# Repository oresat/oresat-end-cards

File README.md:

# "End Card" PCBs for OreSat

OreSat cards in the top position (#1) and bottom position (#20) are special because they interface with
both the solar arrays and with the end caps. They also tend to hold deployable antennas.

## Features

- 4 solar panel connectors
- 3 available RF connectors
- Alternative backplane connectors only (since the solar panel connectors take up the main connector spot)

## Connector information

- TBD.

## LICENSE

Copyright Portland State Aerospace Society 2022.

This documentation describes Open Hardware and is licensed under the CERN OHL v2

You may redistribute and modify this documentation under the terms of the CERN OHL v.1.2. [https://ohwr.org/cernohl](https://ohwr.org/cernohl). This documentation is distributed WITHOUT ANY EXPRESS OR IMPLIED WARRANTY, INCLUDING OF MERCHANTABILITY, SATISFACTORY QUALITY AND FITNESS FOR A PARTICULAR PURPOSE. Please see the CERN OHL v2 for applicable conditions.

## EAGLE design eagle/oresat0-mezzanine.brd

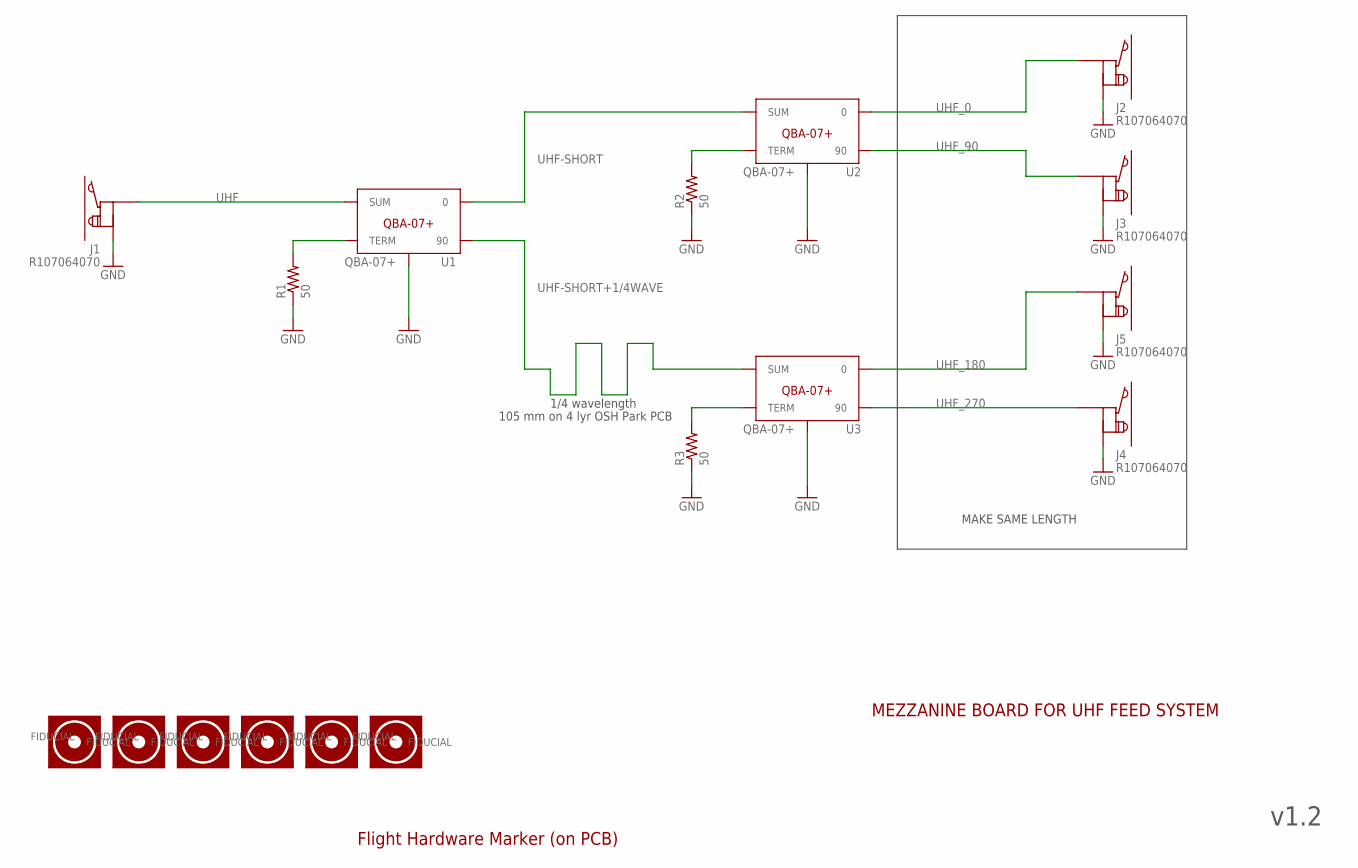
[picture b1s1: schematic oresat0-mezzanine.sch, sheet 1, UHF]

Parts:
FIDUCIAL1, FIDUCIAL2, FIDUCIAL3, FIDUCIAL4, FIDUCIAL6, FIDUCIAL7: FIDUCIAL-1.0X2.0
J1, J2, J3, J4, J5: R107064070; R107064070_SOLDER
R1, R2, R3: 50; .0603-C-NOSILK
U1, U2, U3: QBA-07+
U$1: FLIGHMARKERNEW; FLIGHTMARKER_NEW_BOARDS

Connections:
GND: J1.P$2, J1.P$3, J2.P$2, J2.P$3, J3.P$2, J3.P$3, J4.P$2, J4.P$3, J5.P$2, J5.P$3, R1.1, R2.1, R3.1, U1.2 (GND), U1.3 (GND), U1.4 (GND), U1.7 (GND), U1.8 (GND), U1.9 (GND), U1.GND-NO-PAD (GND), U2.2 (GND), U2.3 (GND), U2.4 (GND), U2.7 (GND), U2.8 (GND), U2.9 (GND), U2.GND-NO-PAD (GND), U3.2 (GND), U3.3 (GND), U3.4 (GND), U3.7 (GND), U3.8 (GND), U3.9 (GND), U3.GND-NO-PAD (GND); also elsewhere on the board
unnamed: R1.2, U1.5 (TERM)
unnamed: R2.2, U2.5 (TERM)
unnamed: R3.2, U3.5 (TERM)
UHF: J1.P$1, U1.1 (SUM)
UHF-SHORT: U1.6 (0), U2.1 (SUM)
UHF-SHORT+1/4WAVE: U1.10 (90), U3.1 (SUM)
UHF_0: J2.P$1, U2.6 (0)
UHF_90: J3.P$1, U2.10 (90)
UHF_180: J5.P$1, U3.6 (0)
UHF_270: J4.P$1, U3.10 (90)

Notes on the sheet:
1/4 wavelength
v1.2
MEZZANINE BOARD FOR UHF FEED SYSTEM
MAKE SAME LENGTH
105 mm on 4 lyr OSH Park PCB

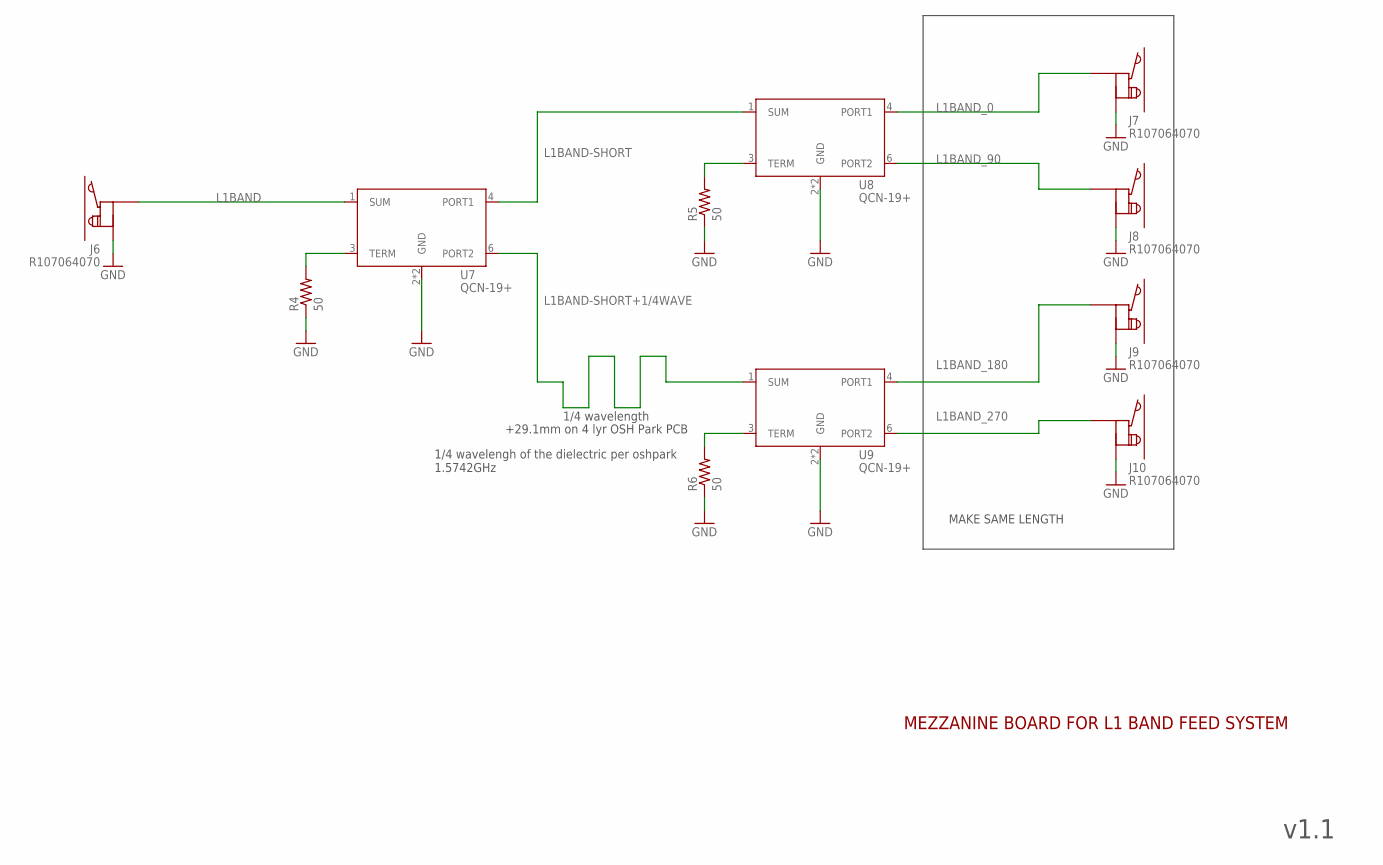
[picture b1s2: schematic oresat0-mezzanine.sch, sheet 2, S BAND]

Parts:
J6, J7, J8, J9, J10: R107064070; R107064070_SOLDER
R4, R5, R6: 50; .0603-C-NOSILK
U7, U8, U9: QCN-19+; QCN-XXX+

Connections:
GND: J6.P$2, J6.P$3, J7.P$2, J7.P$3, J8.P$2, J8.P$3, J9.P$2, J9.P$3, J10.P$2, J10.P$3, R4.1, R5.1, R6.1, U7.2 (GND), U7.5 (GND), U8.2 (GND), U8.5 (GND), U9.2 (GND), U9.5 (GND); also elsewhere on the board
L1BAND: J6.P$1, U7.1 (SUM)
L1BAND-SHORT: U7.4 (PORT1), U8.1 (SUM)
L1BAND-SHORT+1/4WAVE: U7.6 (PORT2), U9.1 (SUM)
L1BAND_0: J7.P$1, U8.4 (PORT1)
L1BAND_90: J8.P$1, U8.6 (PORT2)
L1BAND_180: J9.P$1, U9.4 (PORT1)
L1BAND_270: J10.P$1, U9.6 (PORT2)
unnamed: R4.2, U7.3 (TERM)
unnamed: R5.2, U8.3 (TERM)
unnamed: R6.2, U9.3 (TERM)

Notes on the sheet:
1/4 wavelength
v1.1
MEZZANINE BOARD FOR L1 BAND FEED SYSTEM
+29.1mm on 4 lyr OSH Park PCB
MAKE SAME LENGTH
1/4 wavelengh of the dielectric per oshpark 1.5742GHz

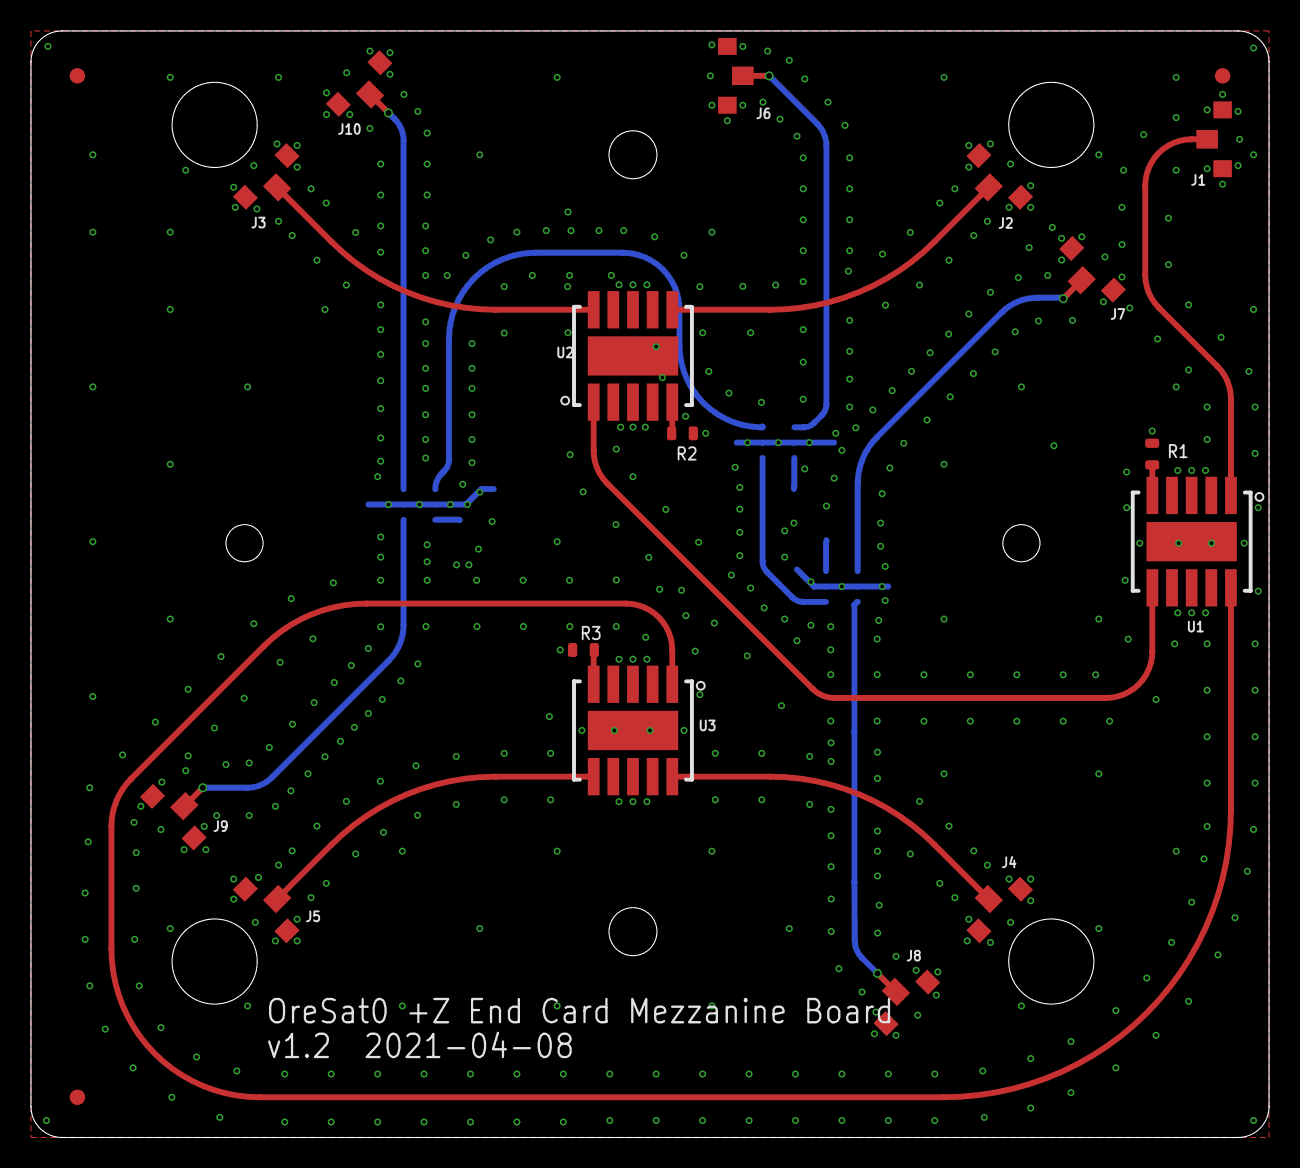
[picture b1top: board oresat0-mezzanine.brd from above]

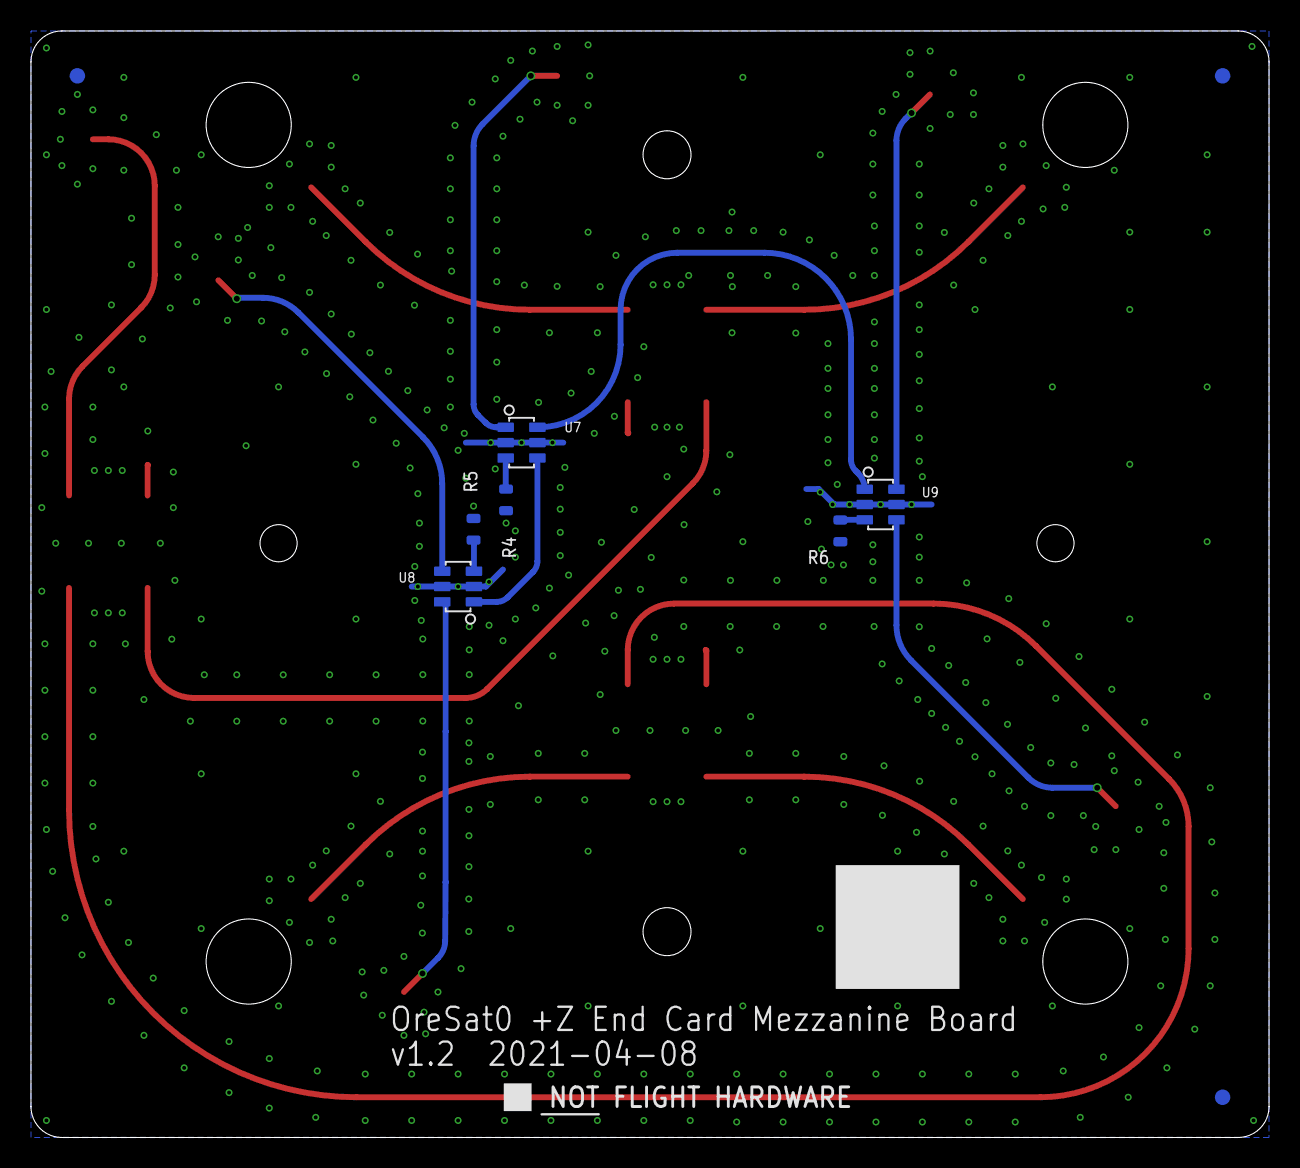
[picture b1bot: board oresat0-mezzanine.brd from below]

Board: 4 copper layers, 80.0 x 71.5 mm, 29 parts (10 on the bottom side), 21 nets.

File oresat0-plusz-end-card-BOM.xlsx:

Bill Of Materials for OreSat0 +Z End Card and Mezzanine
Last modified: 2021/11/01
PCB version: 2.0 |  |  | P/DNP = | Place/Do Not Place (DNP is for final production boards)
BOM revision: 0 |  |  | Generic = | Any generic part with the same characteristics are OK (e.g., bypass cap)
 | +Z END CARD
Cnt | Part References | P/DNP | Mfg | Mfg PN | Description | Generic | Dist | Dist Part Number | Cost | Cost Ext.
1 | CF1 | P | Harwin Inc. | M55-6001242R | 12 Position Receptacle Connector 0.050" (1.27mm) Surface Mount Gold | N | Digi-Key | 952-3835-1-ND | 1.74 | 1.74
3 | CM1, CM2, CM3 | P | Molex | 73300-0020 | SMPM Connector Plug, Male Pin 50Ohm Board Edge | N | Digi-Key | WM10772-ND | 16.41 | 49.230000000000004
4 | HW1, HW2, HW3, HW4 | P | McMaster Carr | 94100A150 | M2 x 0.4 mm 18-8 Stainless Steel Press-Fit Nut | N | McMaster Carr | 94100A150 | 0.56200000000000006 | 2.2480000000000002
4 | J1, J2, J3, J4 | P | Harwin Inc. | M55-7101242R | CONN HEADER SMD R/A 12POS 1.27MM -- Solar connectors | N | Digi-Key | 952-3891-1-ND | 1.46 | 5.8399999999999999
1 | J6 | P | Samtec Inc. | TFM-120-01-L-D-RA | CONN HEADER R/A 40POS 1.27MM - Main OreSat connector | N | Digi-Key | SAM10145-ND | 10.119999999999999 | 10.119999999999999
3 | R1, R2, R3 | P | Vishay Dale | RCP0603W50R0GEB | RES SMD 50 OHM 2% 1.5W 0603 | N | Digi-Key | 541-2655-1-ND | 1.8400000000000001 | 5.5200000000000005
1 | R4 | P | Vishay | PAC100007508FA1000 | Res 7.5 ohm 1W 1% Axial high temperature | N | Digi-Key | PPC1D1.0CT-ND | 0.77000000000000002 | 0.77000000000000002
3 | U1, U2, U3 | P | Mini-Circuits | QCN-19+ | Power Splitter/Combiner, 2 Way-90°, 50Ω, 1100-1925 Mhz, LTCC | N | Mouser | 139-QCN-19 | 13.949999999999999 | 41.849999999999994
 | MEZZANINE
Cnt | Part References | P/DNP | Mfg | Mfg PN | Description | Generic | Dist | Dist Part Number | Cost | Cost Ext.
10 | J1, J2, J3, J4, J5, J6, J7, J8, J9, J10 | P | Radiall | R107064070 | Spring RF connectors | N | Mouser | 501-R107064070 | 5.1500000000000004 | 51.5
6 | R1, R2, R3, R4, R5, R6 | P | Vishay Dale | RCP0603W50R0GEB | RES SMD 50 OHM 2% 1.5W 0603 | N | Digi-Key | 541-2655-1-ND | 1.8400000000000001 | 11.040000000000001
3 | U1, U2, U3 | P | Mini-Circuits | QBA-07+ | Power Splitter/Combiner, 2 Way-90°, 50Ω, 340-680 Mhz, LTCC | N | Mini-Circuits | QBA-07+ | 6.9500000000000002 | 20.850000000000001
3 | U7, U8, U9 | P | Mini-Circuits | QCN-19+ | Power Splitter/Combiner, 2 Way-90°, 50Ω, 1100-1925 Mhz, LTCC | N | Mouser | 139-QCN-19 | 13.949999999999999 | 41.849999999999994
 |  |  |  |  |  |  |  | Total |  | 242.55799999999999

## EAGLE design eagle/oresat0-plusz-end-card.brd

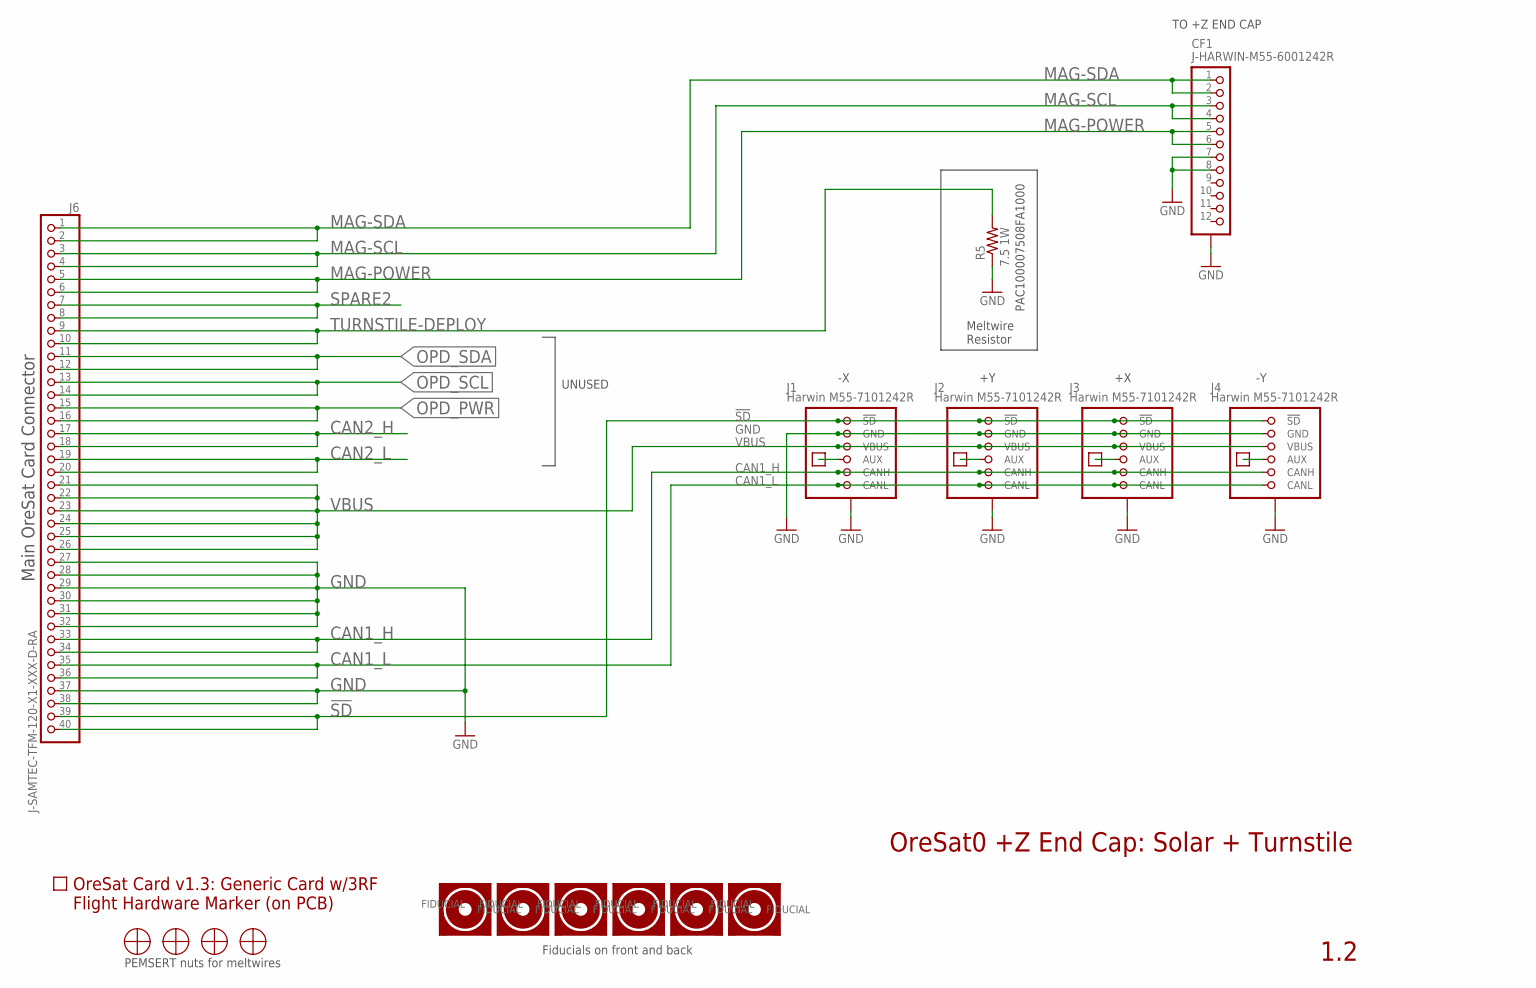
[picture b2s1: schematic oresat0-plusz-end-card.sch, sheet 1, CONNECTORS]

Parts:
CF1: J-HARWIN-M55-6001242R; HARWIN-M55-60X1242R
FIDUCIAL1, FIDUCIAL2, FIDUCIAL3, FIDUCIAL4, FIDUCIAL5, FIDUCIAL6: FIDUCIAL-1.0X2.0
HW1, HW2, HW3, HW4: MCMASTER-94100A150
J1, J2, J3, J4: Harwin M55-7101242R; M55-7101242R
J6: J-SAMTEC-TFM-120-X1-XXX-D-RA; MPN TFM-120-01-L-D-RA
PCB1: ORESAT-CARD-V1.3-GENERIC-3RF
R5: 7.5 1W; PAC100-FOR-MELTWIRE
TP1, TP2, TP3, TP4: TEST-POINT-LARGE-SQUARE; 1X01
U$1: FLIGHMARKERNEW; FLIGHTMARKER_NEW_BOARDS

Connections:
!SD: J1.1 (!SD), J1.2 (!SD), J2.1 (!SD), J2.2 (!SD), J3.1 (!SD), J3.2 (!SD), J4.1 (!SD), J4.2 (!SD), J6.39, J6.40
CAN1_H: J1.9 (CANH), J1.10 (CANH), J2.9 (CANH), J2.10 (CANH), J3.9 (CANH), J3.10 (CANH), J4.9 (CANH), J4.10 (CANH), J6.33, J6.34
CAN1_L: J1.11 (CANL), J1.12 (CANL), J2.11 (CANL), J2.12 (CANL), J3.11 (CANL), J3.12 (CANL), J4.11 (CANL), J4.12 (CANL), J6.35, J6.36
CAN2_H: J6.17, J6.18
CAN2_L: J6.19, J6.20
GND: CF1.7, CF1.8, CF1.P$1 (SHIELDS), CF1.P$2 (SHIELDS), CF1.P$3 (SHIELDS), CF1.P$4 (SHIELDS), J1.3 (GND), J1.4 (GND), J1.P$1 (SHIELD), J1.P$2 (SHIELD), J1.P$3 (SHIELD), J1.P$4 (SHIELD), J2.3 (GND), J2.4 (GND), J2.P$1 (SHIELD), J2.P$2 (SHIELD), J2.P$3 (SHIELD), J2.P$4 (SHIELD), J3.3 (GND), J3.4 (GND), J3.P$1 (SHIELD), J3.P$2 (SHIELD), J3.P$3 (SHIELD), J3.P$4 (SHIELD), J4.3 (GND), J4.4 (GND), J4.P$1 (SHIELD), J4.P$2 (SHIELD), J4.P$3 (SHIELD), J4.P$4 (SHIELD), J6.27, J6.28, J6.29, J6.30, J6.31, J6.32, J6.37, J6.38, R5.P$1 (1), R5.P$2 (1); also elsewhere on the board
MAG-POWER: CF1.5, CF1.6, J6.5, J6.6
MAG-SCL: CF1.3, CF1.4, J6.3, J6.4
MAG-SDA: CF1.1, CF1.2, J6.1, J6.2
unnamed: J1.7 (AUX), J1.8 (AUX), TP1.1
unnamed: J2.7 (AUX), J2.8 (AUX), TP2.1
unnamed: J3.7 (AUX), J3.8 (AUX), TP3.1
unnamed: J4.7 (AUX), J4.8 (AUX), TP4.1
OPD_PWR: J6.15, J6.16
OPD_SCL: J6.13, J6.14
OPD_SDA: J6.11, J6.12
SPARE2: J6.7, J6.8
TURNSTILE-DEPLOY: J6.9, J6.10, R5.P$3 (2), R5.P$4 (2)
VBUS: J1.5 (VBUS), J1.6 (VBUS), J2.5 (VBUS), J2.6 (VBUS), J3.5 (VBUS), J3.6 (VBUS), J4.5 (VBUS), J4.6 (VBUS), J6.21, J6.22, J6.23, J6.24, J6.25, J6.26

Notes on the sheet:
Main OreSat Card Connector
UNUSED
OreSat0 +Z End Cap: Solar + Turnstile
1.2
TO +Z END CAP
PEMSERT nuts for meltwires
PAC100007508FA1000
Meltwire Resistor
Fiducials on front and back

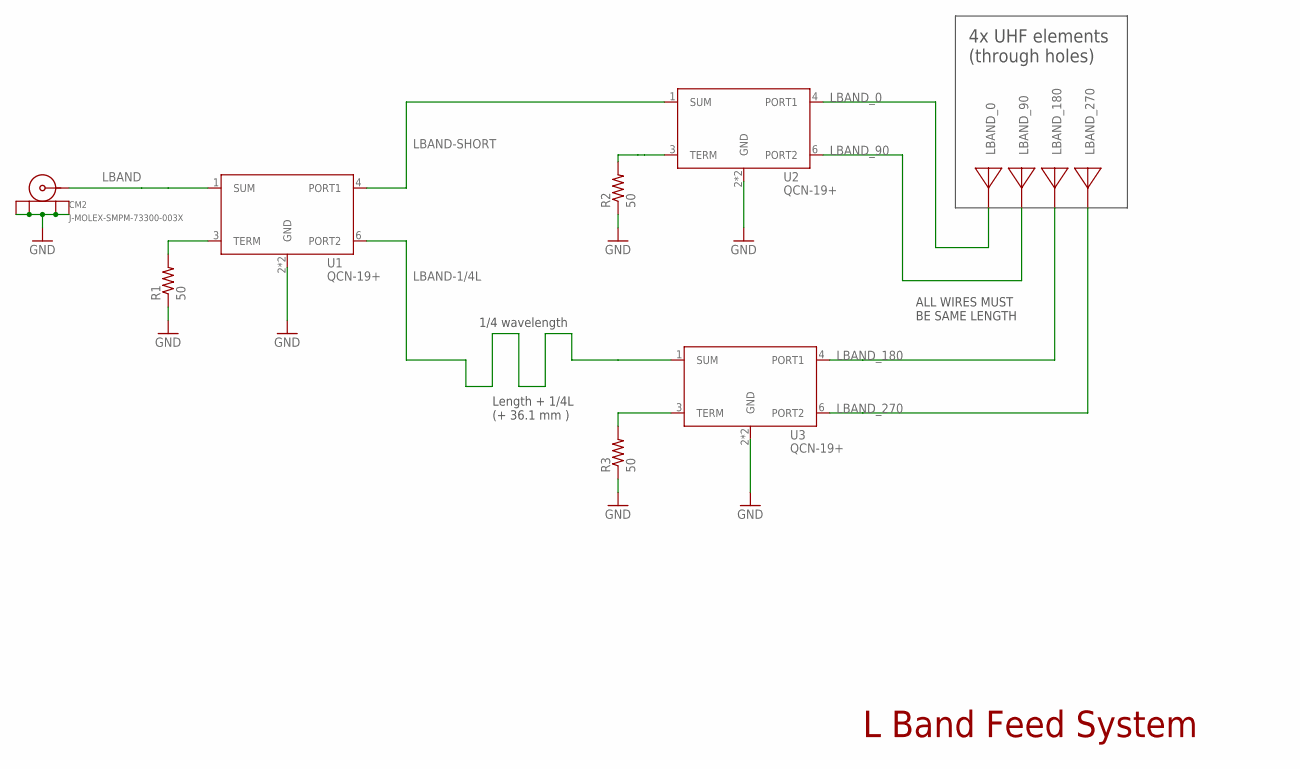
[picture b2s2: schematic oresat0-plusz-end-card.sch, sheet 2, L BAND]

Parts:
CM2: J-MOLEX-SMPM-73300-003X; J-MOLEX-SMPM-073300-003X
R1, R2, R3: 50; .0603-C-NOSILK
U1, U2, U3: QCN-19+; QCN-XXX+

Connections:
GND: CM2.P$1 (SHIELD3), CM2.P$2 (SHIELD2), CM2.P$3 (SHIELD1), CM2.P$4 (SHIELD), R1.1, R2.1, R3.1, U1.2 (GND), U1.5 (GND), U2.2 (GND), U2.5 (GND), U3.2 (GND), U3.5 (GND); also elsewhere on the board
LBAND: CM2.RF (CENTER), U1.1 (SUM)
LBAND-1/4L: U1.6 (PORT2), U3.1 (SUM)
LBAND-SHORT: U1.4 (PORT1), U2.1 (SUM)
LBAND_0: U2.4 (PORT1)
LBAND_90: U2.6 (PORT2)
LBAND_180: U3.4 (PORT1)
LBAND_270: U3.6 (PORT2)
unnamed: R1.2, U1.3 (TERM)
unnamed: R2.2, U2.3 (TERM)
unnamed: R3.2, U3.3 (TERM)

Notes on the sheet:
1/4 wavelength
L Band Feed System
4x UHF elements (through holes)
Length + 1/4L (+ 36.1 mm )
ALL WIRES MUST BE SAME LENGTH

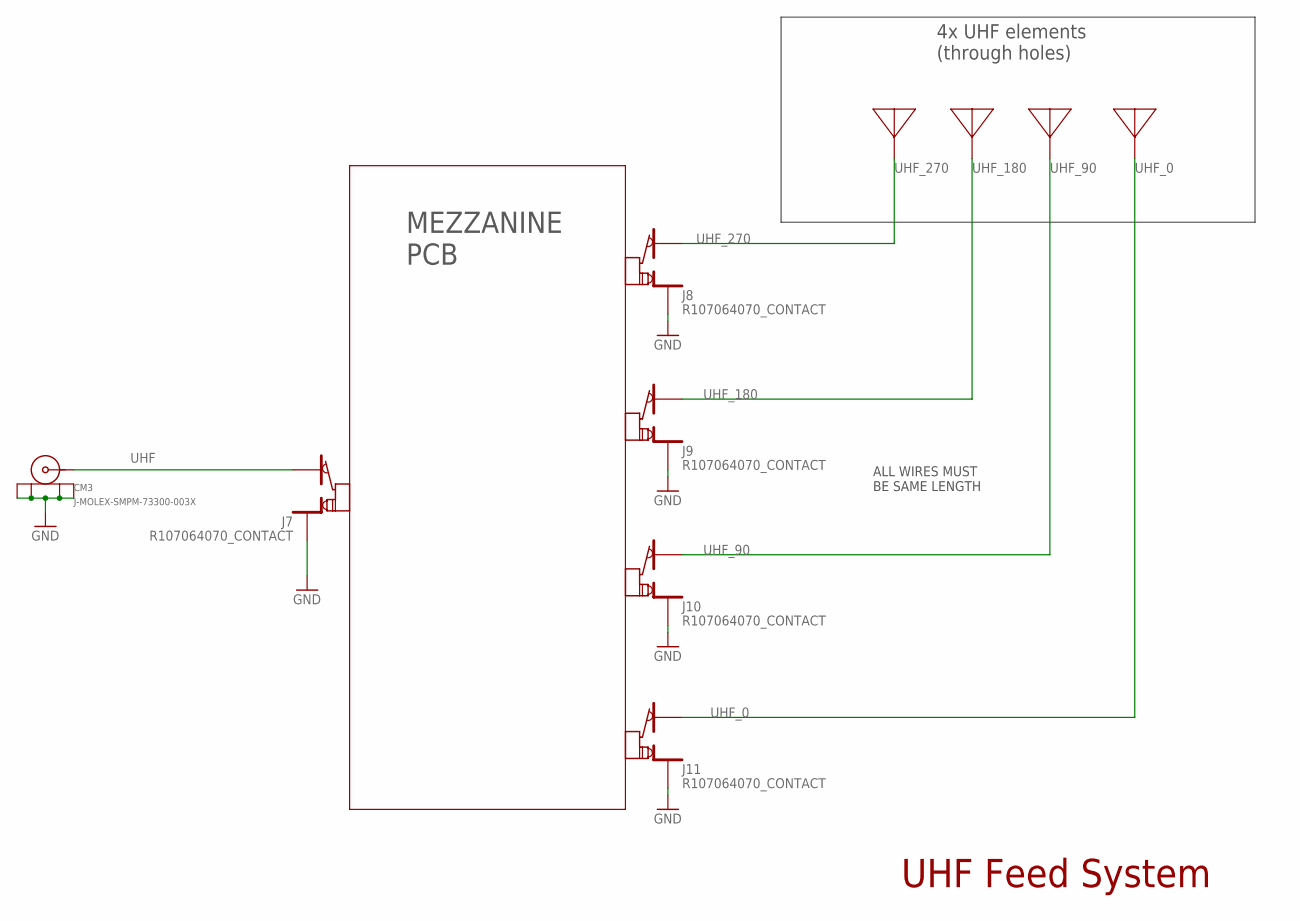
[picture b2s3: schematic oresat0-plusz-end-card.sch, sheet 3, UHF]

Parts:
CM3: J-MOLEX-SMPM-73300-003X; J-MOLEX-SMPM-073300-003X
J7, J8, J9, J10, J11: R107064070_CONTACT

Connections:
GND: CM3.P$1 (SHIELD3), CM3.P$2 (SHIELD2), CM3.P$3 (SHIELD1), CM3.P$4 (SHIELD), J7.P$2, J7.P$3, J8.P$2, J8.P$3, J9.P$2, J9.P$3, J10.P$2, J10.P$3, J11.P$2, J11.P$3; also elsewhere on the board
UHF: CM3.RF (CENTER), J7.P$1
UHF_0: J11.P$1
UHF_90: J10.P$1
UHF_180: J9.P$1
UHF_270: J8.P$1

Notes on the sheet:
MEZZANINE PCB
UHF Feed System
4x UHF elements (through holes)
ALL WIRES MUST BE SAME LENGTH

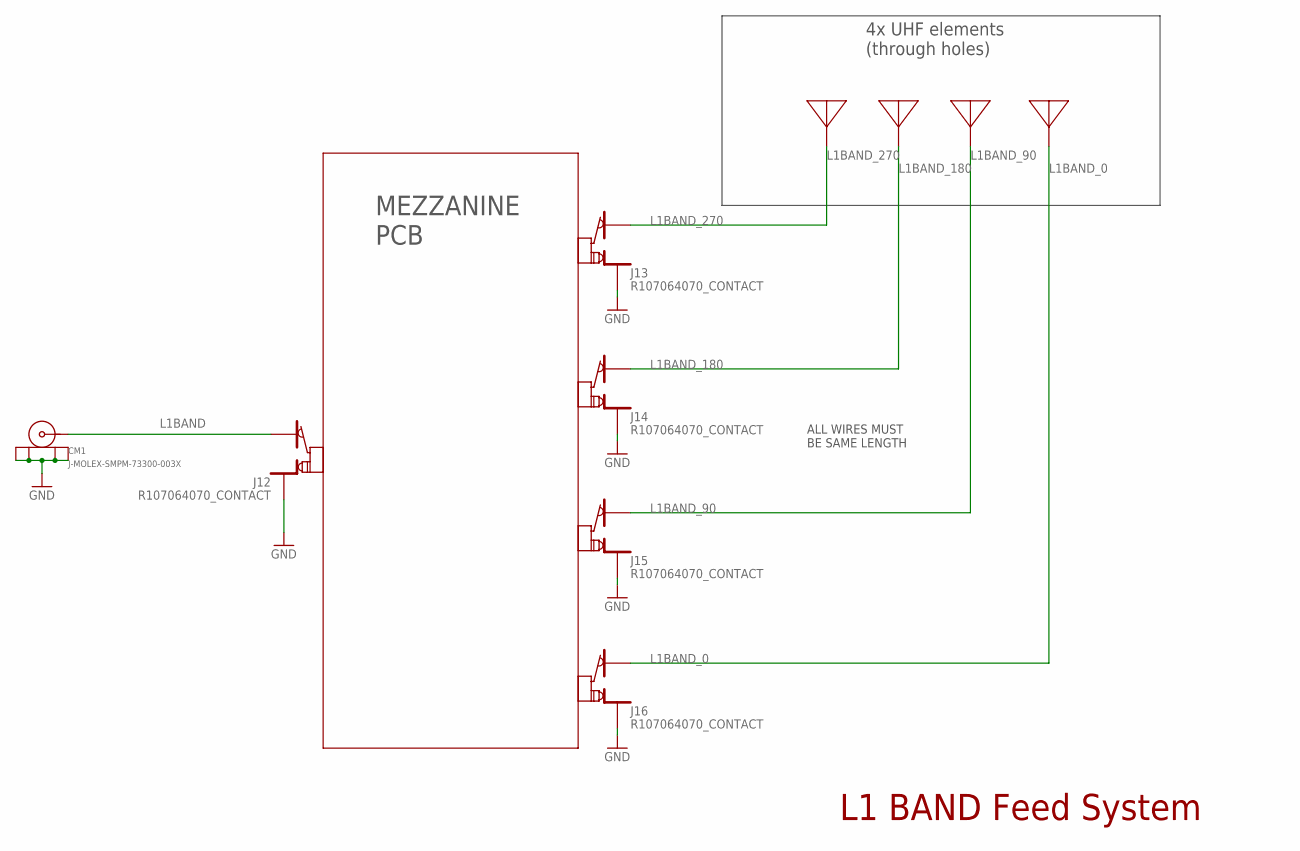
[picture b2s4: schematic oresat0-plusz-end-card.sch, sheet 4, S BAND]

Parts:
CM1: J-MOLEX-SMPM-73300-003X; J-MOLEX-SMPM-073300-003X
J12, J13, J14, J15, J16: R107064070_CONTACT

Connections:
GND: CM1.P$1 (SHIELD3), CM1.P$2 (SHIELD2), CM1.P$3 (SHIELD1), CM1.P$4 (SHIELD), J12.P$2, J12.P$3, J13.P$2, J13.P$3, J14.P$2, J14.P$3, J15.P$2, J15.P$3, J16.P$2, J16.P$3; also elsewhere on the board
L1BAND: CM1.RF (CENTER), J12.P$1
L1BAND_0: J16.P$1
L1BAND_90: J15.P$1
L1BAND_180: J14.P$1
L1BAND_270: J13.P$1

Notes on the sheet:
MEZZANINE PCB
L1 BAND Feed System
4x UHF elements (through holes)
ALL WIRES MUST BE SAME LENGTH

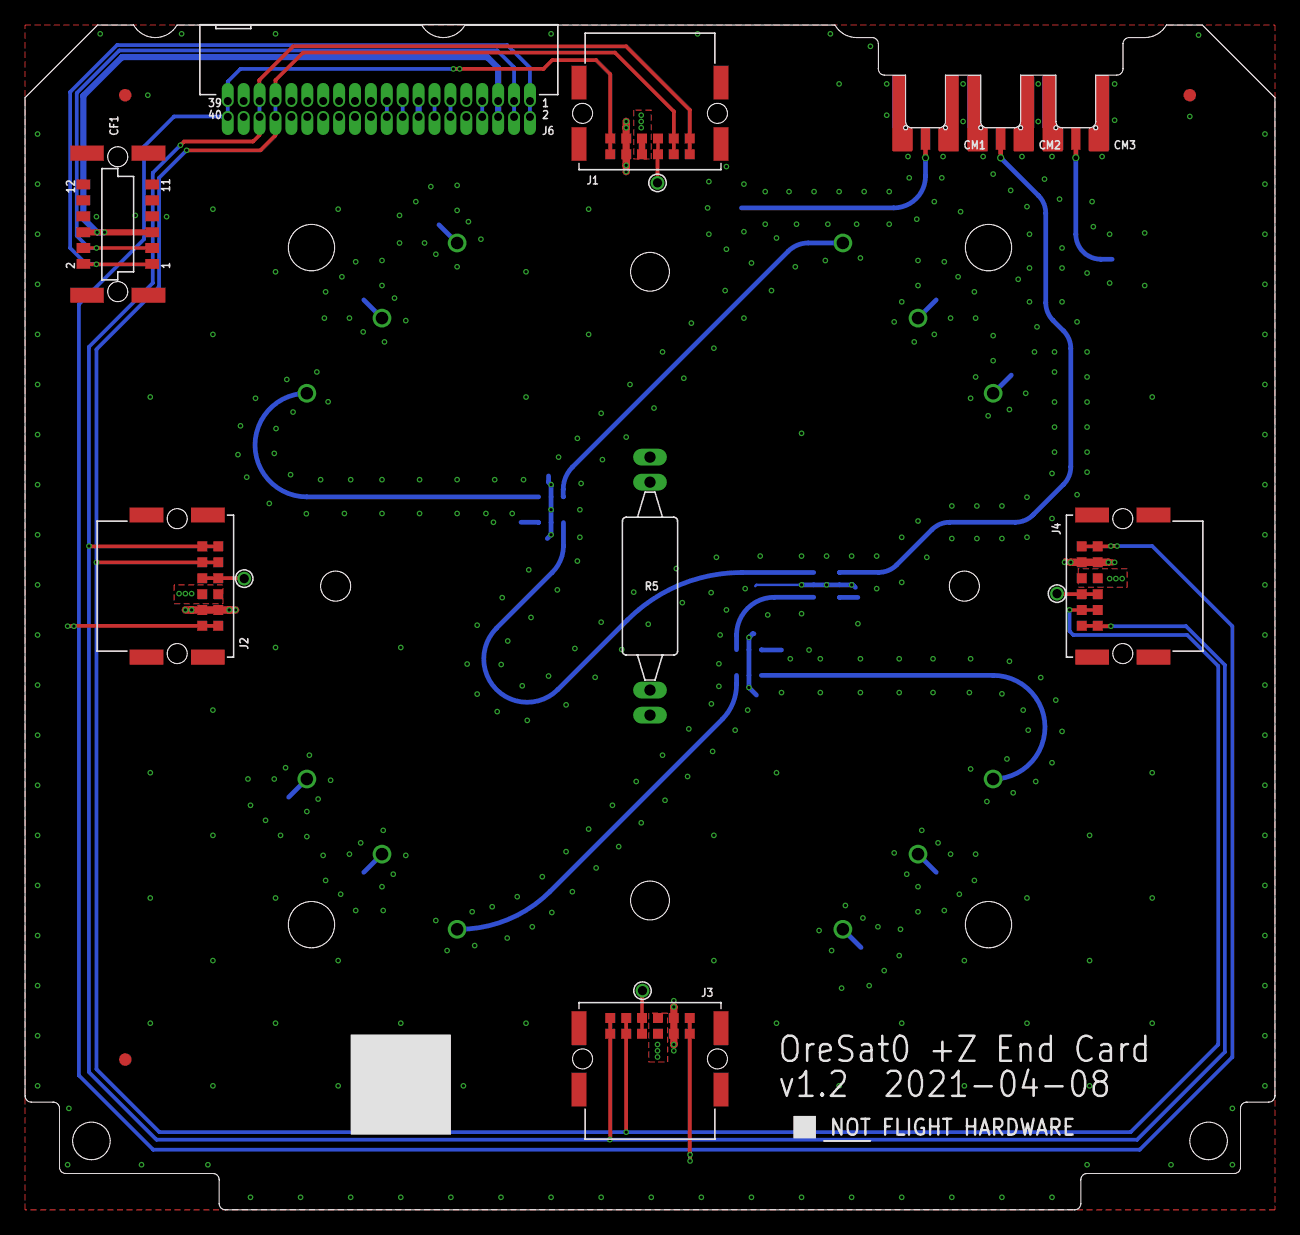
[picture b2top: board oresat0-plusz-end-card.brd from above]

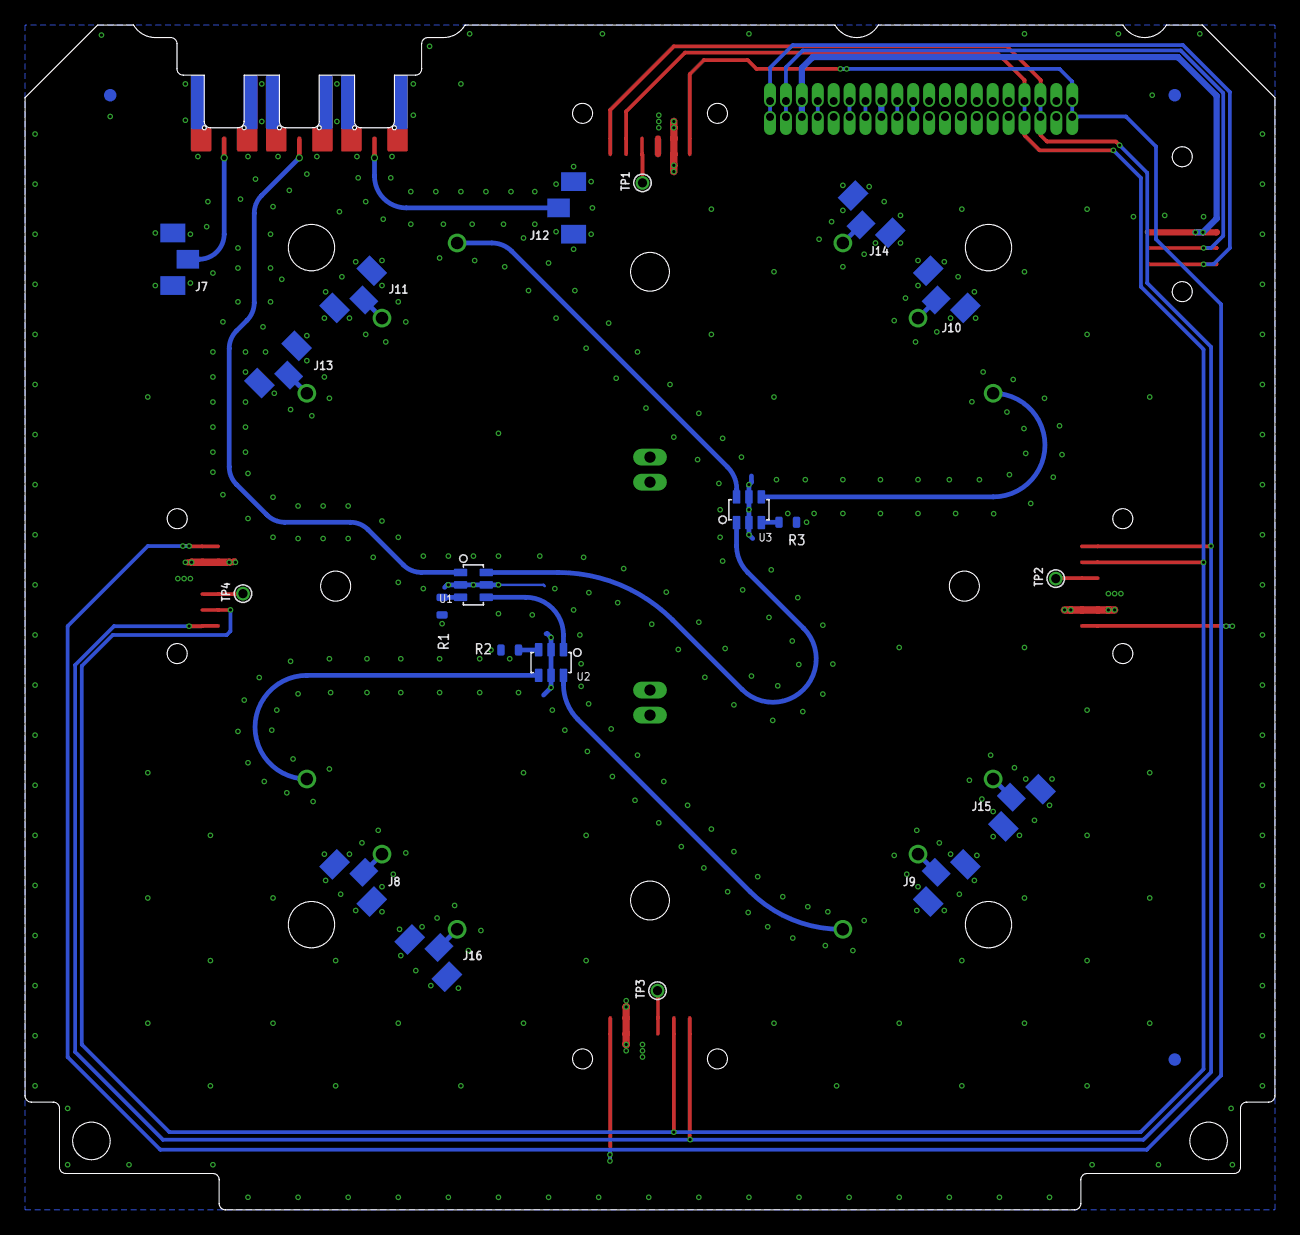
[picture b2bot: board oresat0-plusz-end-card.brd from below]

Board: 4 copper layers, 99.8 x 94.6 mm, 42 parts (19 on the bottom side), 27 nets.

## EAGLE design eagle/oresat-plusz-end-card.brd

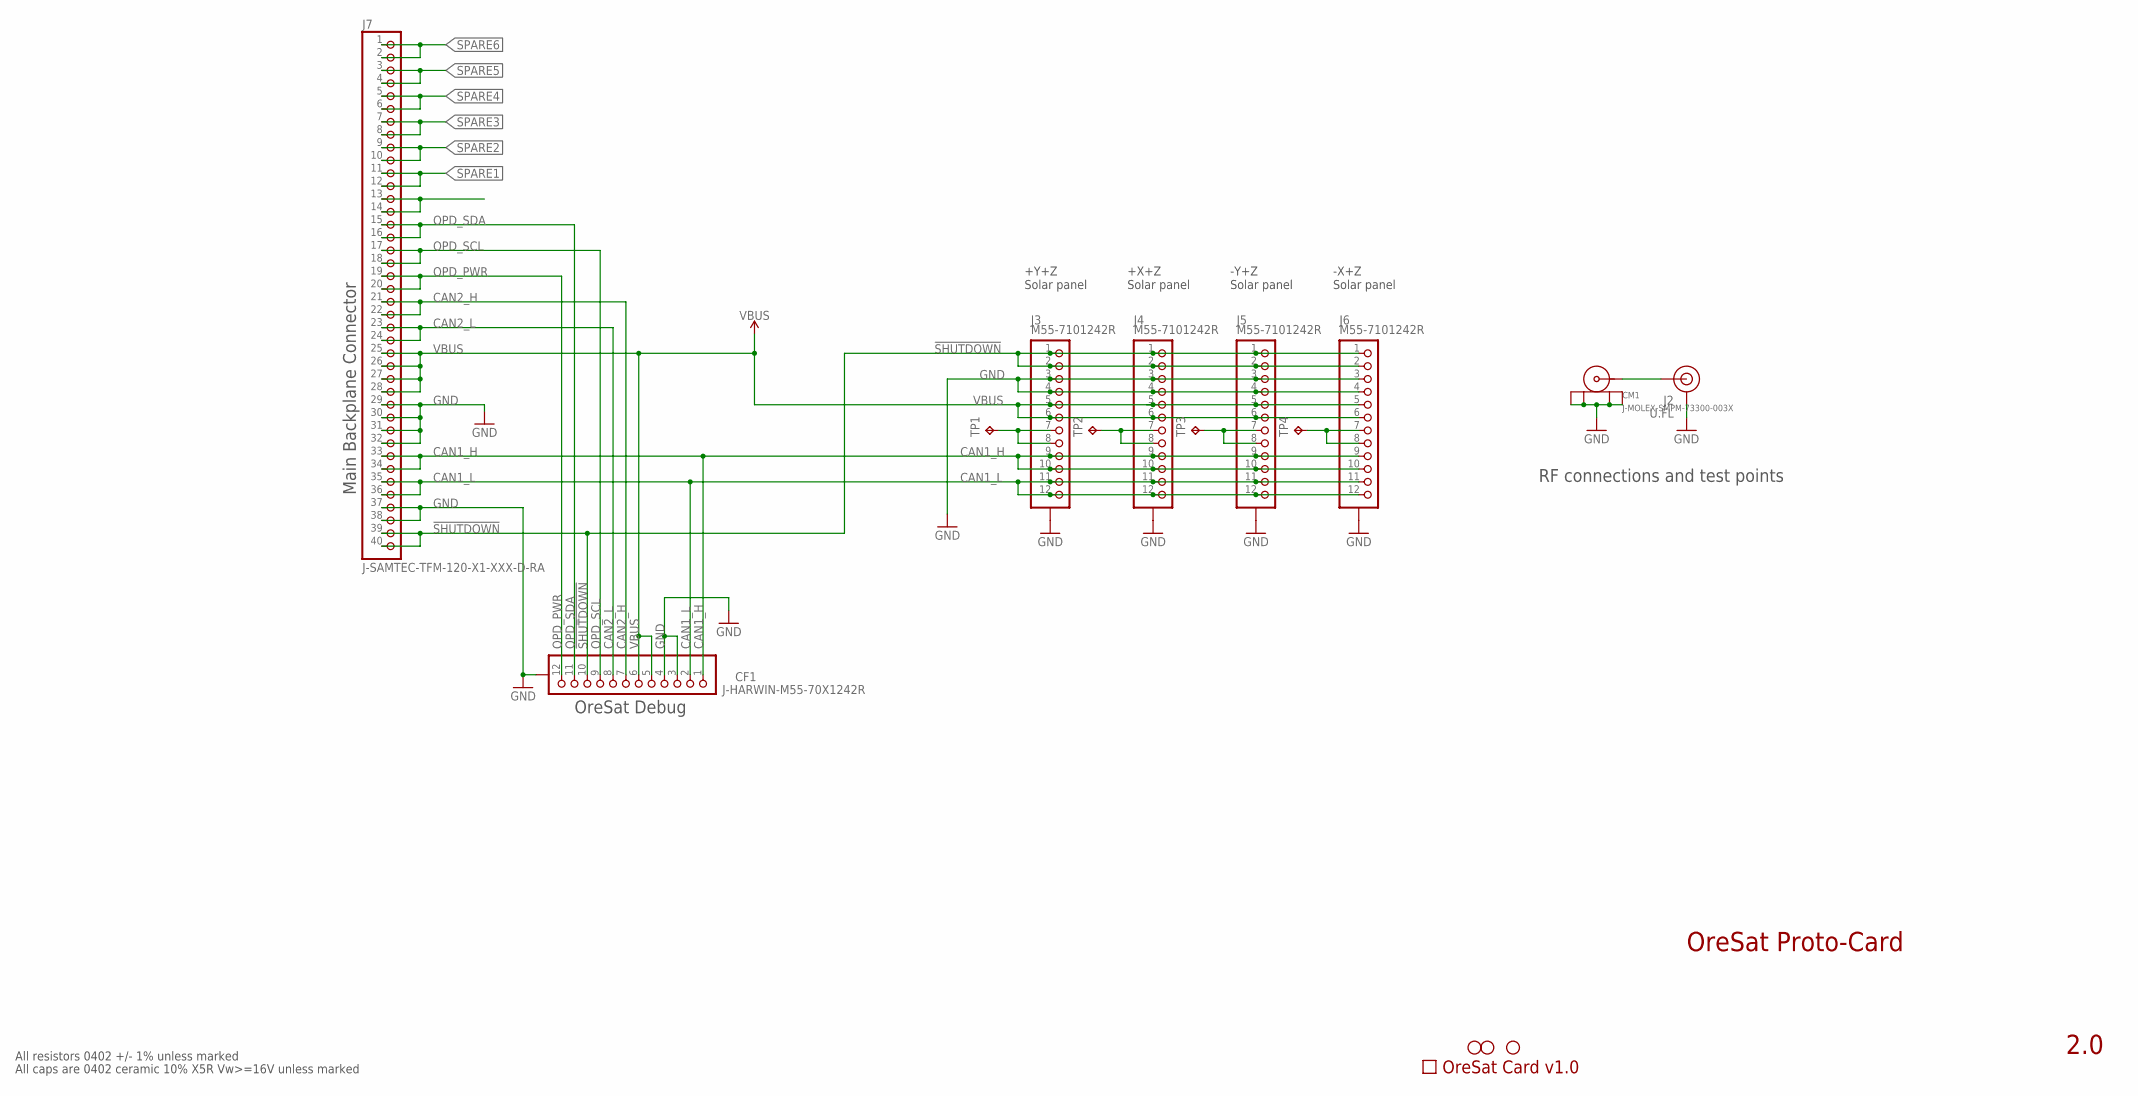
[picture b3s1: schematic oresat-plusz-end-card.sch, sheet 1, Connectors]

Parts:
CARD: ORESAT-CARD-V0.5; ORESAT-CARD-V1.0
CF1: J-HARWIN-M55-70X1242R; HARWIN-M55-70X1242R
CM1: J-MOLEX-SMPM-73300-003X; J-MOLEX-SMPM-073300-003X
H1, H2, H4: STAND-OFFTIGHT; STAND-OFF-TIGHT
J2: U.FL
J3, J4, J5, J6: M55-7101242R
J7: J-SAMTEC-TFM-120-X1-XXX-D-RA
TP1, TP2, TP3, TP4: TPPAD1-13; P1-13

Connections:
!SHUTDOWN: CF1.10, J3.1, J3.2, J4.1, J4.2, J5.1, J5.2, J6.1, J6.2, J7.39, J7.40
CAN1_H: CF1.1, J3.9, J3.10, J4.9, J4.10, J5.9, J5.10, J6.9, J6.10, J7.33, J7.34; also elsewhere on the board
CAN1_L: CF1.2, J3.11, J3.12, J4.11, J4.12, J5.11, J5.12, J6.11, J6.12, J7.35, J7.36; also elsewhere on the board
CAN2_H: CF1.7, J7.21, J7.22
CAN2_L: CF1.8, J7.23, J7.24
GND: CF1.3, CF1.4, CF1.P$1 (SHIELDS), CF1.P$2 (SHIELDS), CF1.P$3 (SHIELDS), CF1.P$4 (SHIELDS), CM1.P$1 (SHIELD3), CM1.P$2 (SHIELD2), CM1.P$3 (SHIELD1), CM1.P$4 (SHIELD), J2.1 (GND), J2.2 (GND), J3.3, J3.4, J3.P$1 (SHIELD), J3.P$2 (SHIELD), J3.P$3 (SHIELD), J3.P$4 (SHIELD), J4.3, J4.4, J4.P$1 (SHIELD), J4.P$2 (SHIELD), J4.P$3 (SHIELD), J4.P$4 (SHIELD), J5.3, J5.4, J5.P$1 (SHIELD), J5.P$2 (SHIELD), J5.P$3 (SHIELD), J5.P$4 (SHIELD), J6.3, J6.4, J6.P$1 (SHIELD), J6.P$2 (SHIELD), J6.P$3 (SHIELD), J6.P$4 (SHIELD), J7.29, J7.30, J7.31, J7.32, J7.37, J7.38; also elsewhere on the board
unnamed: J4.7, J4.8, TP2.TP
unnamed: J3.7, J3.8, TP1.TP
unnamed: J5.7, J5.8, TP3.TP
unnamed: J6.7, J6.8, TP4.TP
unnamed: J7.13, J7.14
OPD_PWR: CF1.12, J7.19, J7.20; also elsewhere on the board
OPD_SCL: CF1.9, J7.17, J7.18; also elsewhere on the board
OPD_SDA: CF1.11, J7.15, J7.16; also elsewhere on the board
RF1: CM1.RF (CENTER), J2.FEED (SIGNAL)
SPARE1: J7.11, J7.12
SPARE2: J7.9, J7.10
SPARE3: J7.7, J7.8
SPARE4: J7.5, J7.6
SPARE5: J7.3, J7.4
SPARE6: J7.1, J7.2
VBUS: CF1.5, CF1.6, J3.5, J3.6, J4.5, J4.6, J5.5, J5.6, J6.5, J6.6, J7.25, J7.26, J7.27, J7.28; also elsewhere on the board

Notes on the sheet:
OreSat Proto-Card
2.0
All resistors 0402 +/- 1% unless marked
All caps are 0402 ceramic 10% X5R Vw>=16V unless marked
Main Backplane Connector
RF connections and test points
+X+Z Solar panel
-X+Z Solar panel
+Y+Z Solar panel
-Y+Z Solar panel
OreSat Debug

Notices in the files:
parts and their libraries:
SparkFun-Connectors: Licensing: Creative Commons ShareAlike 4.0 International - https://creativecommons.org/licenses/by-sa/4.0
